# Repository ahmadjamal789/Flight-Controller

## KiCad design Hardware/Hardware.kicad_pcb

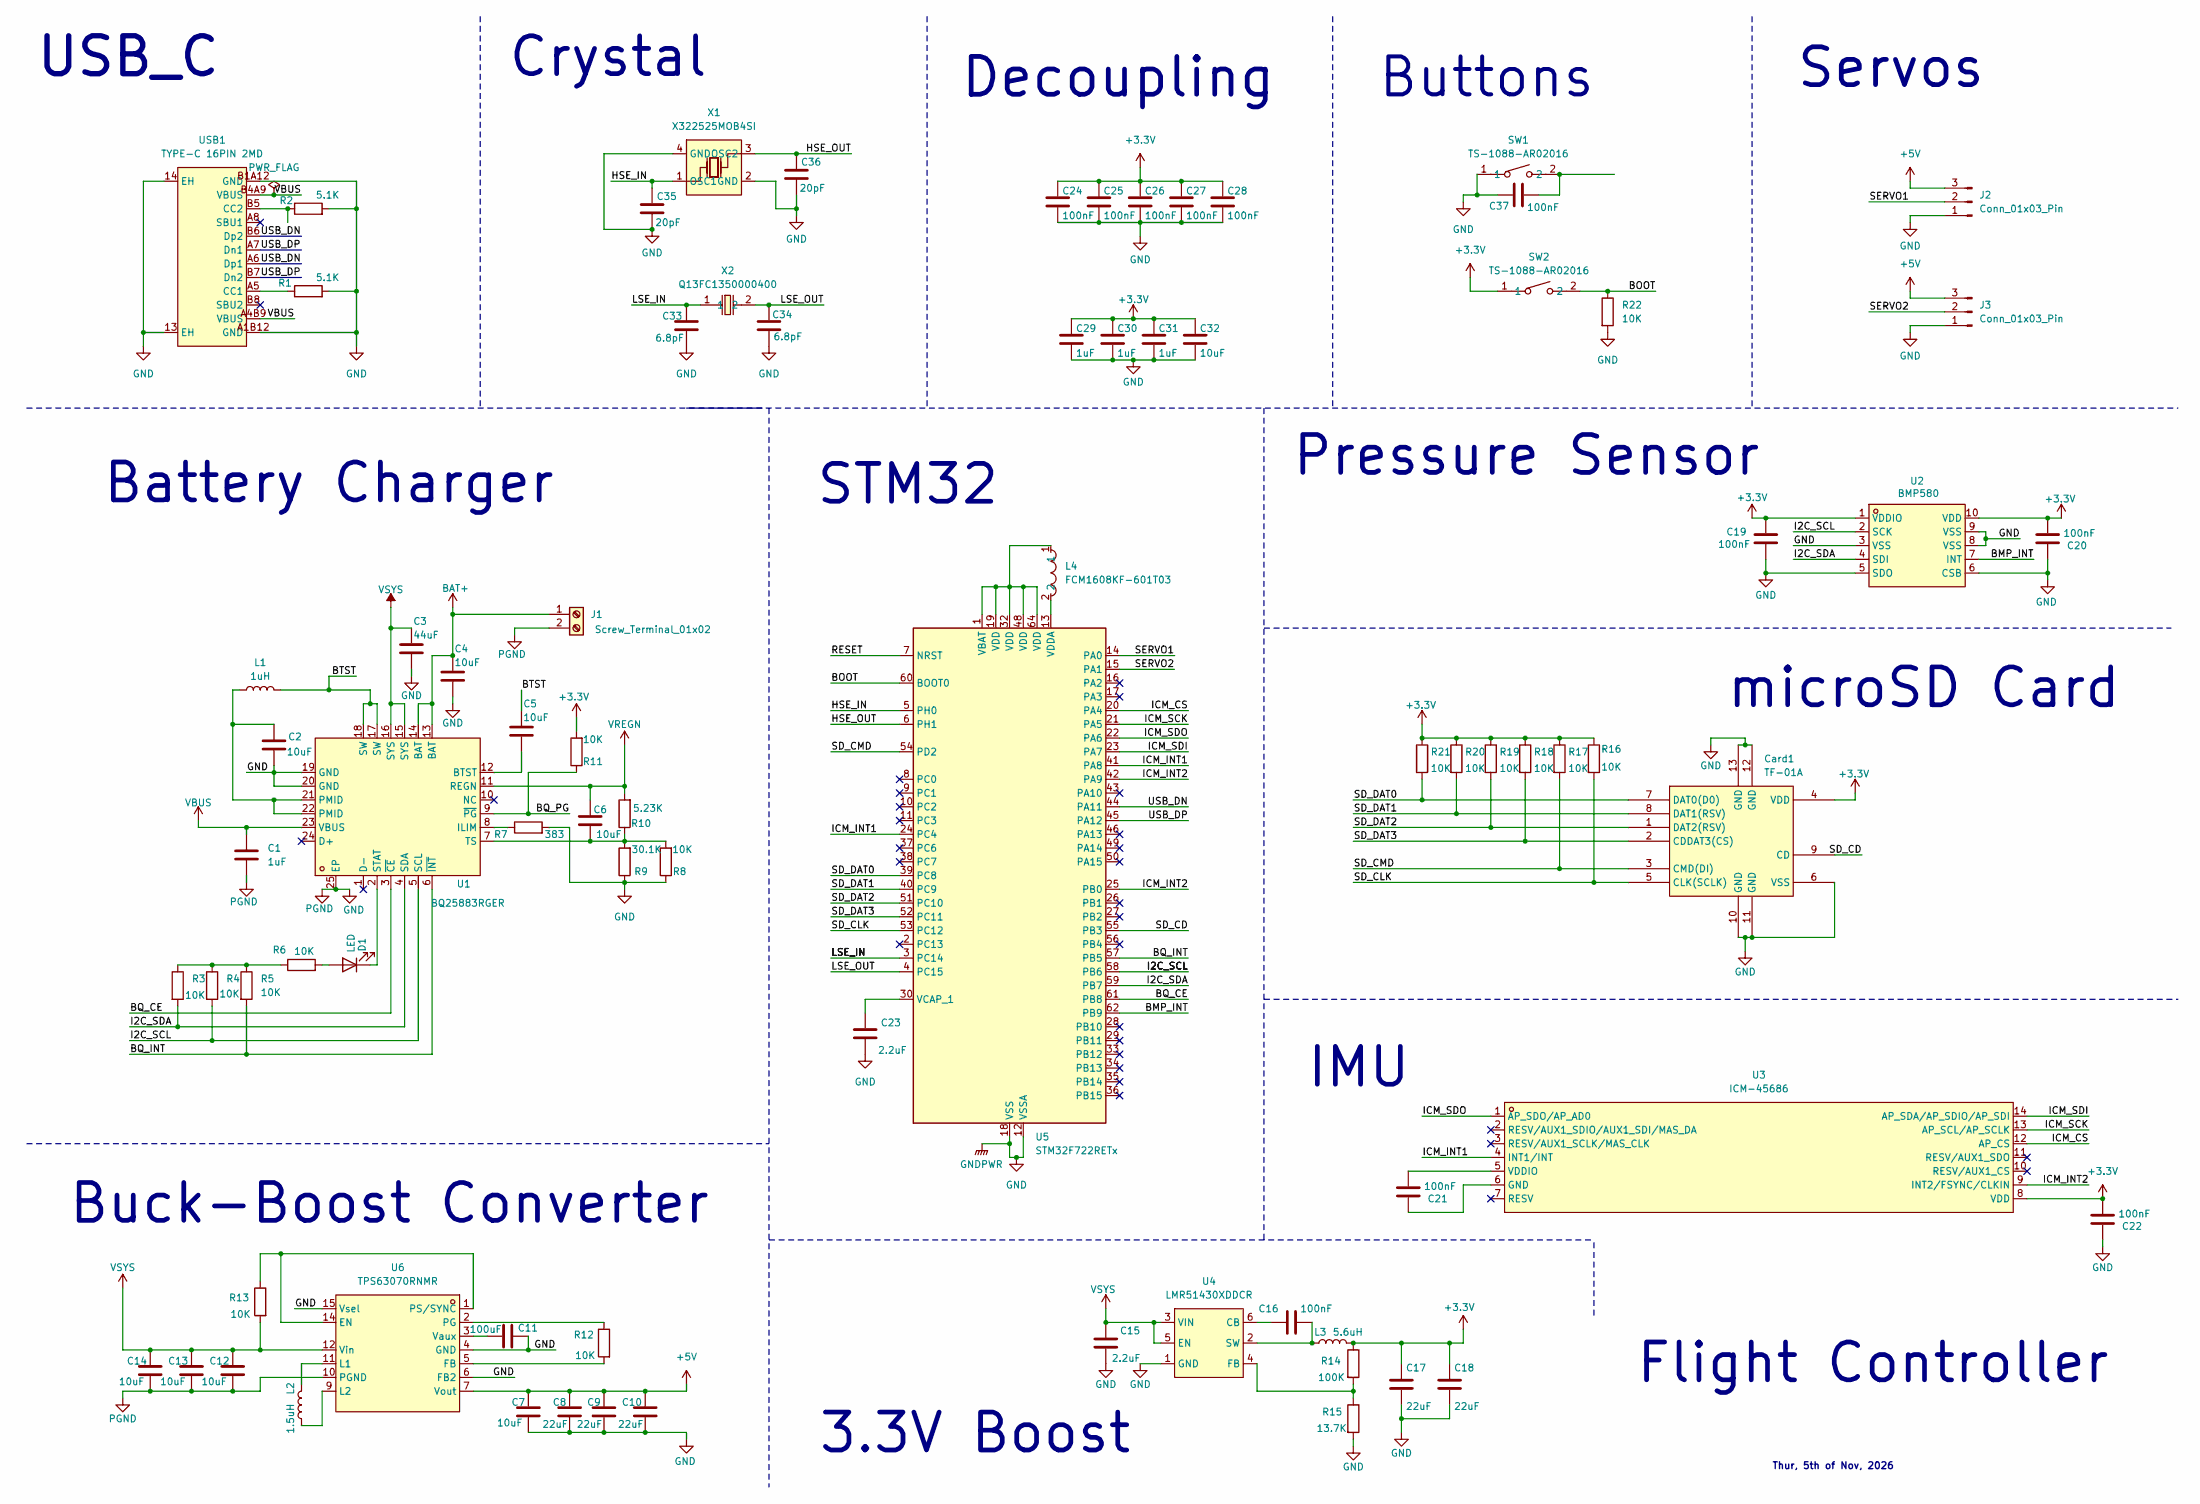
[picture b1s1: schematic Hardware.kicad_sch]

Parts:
C1, C29, C30: 1uF; C_0402_1005Metric
C2, C4, C5, C6, C7, C12, C13, C14, C32: 10uF; C_0805_2012Metric
C3: 44uF; C_0805_2012Metric
C8, C9, C10: 22uF; C_0805_2012Metric
C11: 100uF; C_01005_0402Metric
C15: 2.2uF; C_0201_0603Metric
C16, C19, C20, C21, C22, C24, C25, C26, C27, C28, C37: 100nF; C_0402_1005Metric
C17, C18: 22uF; C_0402_1005Metric
C23: 2.2uF; C_0402_1005Metric
C31: 1uF; C_0201_0603Metric
C33, C34: 6.8pF; C_0402_1005Metric
C35, C36: 20pF; C_0402_1005Metric
Card1: TF-01A; TF-SMD_TF-01A; MPN TF-01A; LCSC Part C91145
D1: LED; LED_0201_0603Metric
J1: Screw_Terminal_01x02; TerminalBlock_Xinya_XY308-2.54-2P_1x02_P2.54mm_Horizontal
J2, J3: Conn_01x03_Pin; PinHeader_1x03_P2.54mm_Vertical
L1: 1uH; L0603
L2: 1.5uH; L0603
L3: 5.6uH; L0603
L4: FCM1608KF-601T03; L0603; MPN FCM1608KF-601T03; LCSC Part C141723
R1, R2: 5.1K; R_0402_1005Metric
R3, R4, R5, R6, R8, R11, R12, R13, R16, R17, R18, R19, R20, R21, R22: 10K; R_0201_0603Metric
R7: 383; R_0201_0603Metric
R9: 30.1K; R_0402_1005Metric
R10: 5.23K; R_0201_0603Metric
R14: 100K; R_0402_1005Metric
R15: 13.7K; R_0201_0603Metric
SW1, SW2: TS-1088-AR02016; SW-SMD_L3.9-W3.0-P4.45; MPN TS-1088-AR02016; LCSC Part C720477
U1: BQ25883RGER; VFQFPN-24_L4.0-W4.0-P0.50-BL-EP2.8; MPN BQ25883RGER; LCSC Part C544362
U2: BMP580; LGA-10_L2.0-W2.0-P0.50-TL_BMP580; MPN BMP580; LCSC Part C22391138
U3: ICM-45686; LGA-14_L3.0-W2.5-P0.50-TL; MPN ICM-45686; LCSC Part C22459454
U4: LMR51430XDDCR; SOT-23-6_L2.9-W1.6-P0.95-LS2.8-BL; MPN LMR51430XDDCR; LCSC Part C5185863
U5: STM32F722RETx; LQFP-64_10x10mm_P0.5mm
U6: TPS63070RNMR; VQFN-15_L3.0-W2.5-P0.50-BL; MPN TPS63070RNMR; LCSC Part C109322
USB1: TYPE-C 16PIN 2MD; USB-C-SMD_TYPE-C-16PIN-2MD-073; MPN TYPE-C 16PIN 2MD(073); LCSC Part C2765186
X1: X322525MOB4SI; CRYSTAL-SMD_4P-L3.2-W2.5-BL; MPN X322525MOB4SI; LCSC Part C9006
X2: Q13FC1350000400; FC-135R_L3.2-W1.5; MPN Q13FC13500004; LCSC Part C32346

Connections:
+3.3V: C17.1, C18.1, C19.1, C20.2, C22.2, C24.1, C25.1, C26.1, C27.1, C28.1, C29.1, C30.1, C31.1, C32.1, Card1.4 (VDD), L3.2, R11.2, R14.1, R16.1, R17.1, R18.1, R19.1, R20.1, R21.1, SW2.1, U2.1 (VDDIO), U2.10 (VDD), U3.8 (VDD)
+5V: C7.1, C8.1, C9.1, C10.1, J2.3, J3.3, U6.7 (Vout)
/BMP_INT: U2.7 (INT), U5.62 (PB9)
/BOOT: R22.1, SW2.2, U5.60 (BOOT0)
/BQ_CE: U1.3 (~CE), U5.61 (PB8)
/BQ_INT: R5.2, U1.6 (~INT), U5.57 (PB5)
/BQ_PG: R11.1, U1.9 (~PG)
/BTST: C5.1, L1.2, U1.17 (SW), U1.18 (SW)
/HSE_IN: C35.1, U5.5 (PH0), X1.1 (OSC1)
/HSE_OUT: C36.1, U5.6 (PH1), X1.3 (OSC2)
/I2C_SCL: R4.2, U1.5 (SCL), U2.2 (SCK), U5.58 (PB6)
/I2C_SDA: R3.2, U1.4 (SDA), U2.4 (SDI), U5.59 (PB7)
/ICM_CS: U3.12 (AP_CS), U5.20 (PA4)
/ICM_INT1: U3.4 (INT1/INT), U5.24 (PC4), U5.41 (PA8)
/ICM_INT2: U3.9 (INT2/FSYNC/CLKIN), U5.25 (PB0), U5.42 (PA9)
/ICM_SCK: U3.13 (AP_SCL/AP_SCLK), U5.21 (PA5)
/ICM_SDI: U3.14 (AP_SDA/AP_SDIO/AP_SDI), U5.23 (PA7)
/ICM_SDO: U3.1 (AP_SDO/AP_AD0), U5.22 (PA6)
/LSE_IN: C33.1, U5.3 (PC14), X2.1
/LSE_OUT: C34.1, U5.4 (PC15), X2.2
/RESET: U5.7 (NRST)
/SD_CD: Card1.9 (CD), U5.55 (PB3)
/SD_CLK: Card1.5 (CLK(SCLK)), R16.2, U5.53 (PC12)
/SD_CMD: Card1.3 (CMD(DI)), R17.2, U5.54 (PD2)
/SD_DAT0: Card1.7 (DAT0(D0)), R21.2, U5.39 (PC8)
/SD_DAT1: Card1.8 (DAT1(RSV)), R20.2, U5.40 (PC9)
/SD_DAT2: Card1.1 (DAT2(RSV)), R19.2, U5.51 (PC10)
/SD_DAT3: Card1.2 (CDDAT3(CS)), R18.2, U5.52 (PC11)
/SERVO1: J2.2, U5.14 (PA0)
/SERVO2: J3.2, U5.15 (PA1)
/USB_DN: U5.44 (PA11), USB1.A6 (Dp1), USB1.B6 (Dp2)
/USB_DP: U5.45 (PA12), USB1.A7 (Dn1), USB1.B7 (Dn2)
BAT+: C4.1, J1.1, U1.13 (BAT), U1.14 (BAT)
GND: C1.2, C2.2, C3.2, C4.2, C7.2, C8.2, C9.2, C10.2, C11.1, C12.2, C13.2, C14.2, C15.2, C17.2, C18.2, C19.2, C20.1, C22.1, C23.2, C24.2, C25.2, C26.2, C27.2, C28.2, C29.2, C30.2, C31.2, C32.2, C33.2, C34.2, C35.2, C36.2, C37.1, Card1.6 (VSS), Card1.10 (GND), Card1.11 (GND), Card1.12 (GND), Card1.13 (GND), J1.2, J2.1, J3.1, R1.2, R2.2, R7.2, R8.1, R9.1, R15.2, R22.2, SW1.1, U1.19 (GND), U1.20 (GND), U1.25 (EP), U2.3 (VSS), U2.5 (SDO), U2.6 (CSB), U2.8 (VSS), U2.9 (VSS), U4.1 (GND), U5.12 (VSSA), U5.18 (VSS), U5.31 (VSS), U5.47 (VSS), U5.63 (VSS), U6.4 (GND), U6.6 (FB2), U6.10 (PGND), U6.15 (Vsel), USB1.13 (EH), USB1.14 (EH), USB1.A1B12 (GND), USB1.B1A12 (GND), X1.2 (GND), X1.4 (GND)
unnamed: C2.1, L1.1, U1.21 (PMID), U1.22 (PMID)
unnamed: C37.2, SW1.2
unnamed: D1.2 (A), R6.2
unnamed: D1.1 (K), U1.2 (STAT)
unnamed: R3.1, R4.1, R5.1, R6.1
unnamed: C5.2, U1.12 (BTST)
unnamed: R7.1, U1.8 (ILIM)
unnamed: C6.2, R8.2, R9.2, R10.1, U1.7 (TS)
unnamed: C21.1, U3.6 (GND)
unnamed: C21.2, U3.5 (VDDIO)
unnamed: C16.1, U4.6 (CB)
unnamed: R14.2, R15.1, U4.4 (FB)
unnamed: C16.2, L3.1, U4.2 (SW)
unnamed: L4.1, U5.1 (VBAT), U5.19 (VDD), U5.32 (VDD), U5.48 (VDD), U5.64 (VDD)
unnamed: C23.1, U5.30 (VCAP_1)
unnamed: L4.2, U5.13 (VDDA)
unnamed: R13.1, U6.1 (PS/SYNC), U6.14 (EN)
unnamed: R12.2, U6.5 (FB)
unnamed: L2.1, U6.11 (L1)
unnamed: L2.2, U6.9 (L2)
unnamed: R12.1, U6.2 (PG)
unnamed: C11.2, U6.3 (Vaux)
unnamed: R1.1, USB1.A5 (CC1)
unnamed: R2.1, USB1.B5 (CC2)
VBUS: C1.1, U1.23 (VBUS), USB1.A4B9 (VBUS), USB1.B4A9 (VBUS)
VREGN: C6.1, R10.2, U1.11 (REGN)
VSYS: C3.1, C12.1, C13.1, C14.1, C15.1, R13.2, U1.15 (SYS), U1.16 (SYS), U4.3 (VIN), U4.5 (EN), U6.12 (Vin)

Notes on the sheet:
Pressure Sensor
IMU
STM32
USB_C
Thur, 5th of Nov, 2026
Buck-Boost Converter
3.3V Boost
Buttons
Flight Controller
Crystal
Battery Charger
Servos
microSD Card
Decoupling

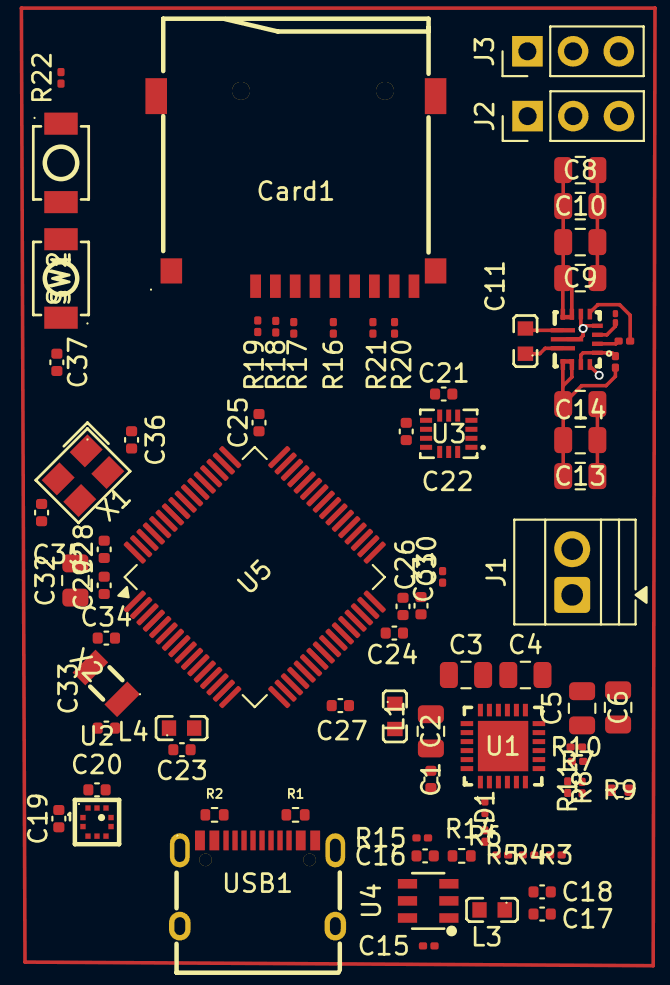
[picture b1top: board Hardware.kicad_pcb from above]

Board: 2 copper layers, 79 parts (0 on the bottom side), 60 nets.

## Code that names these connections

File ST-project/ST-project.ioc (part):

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Mcu.Name=STM32F722R(C-E)Tx
Mcu.Package=LQFP64
Mcu.UserName=STM32F722RETx
PA0-WKUP.Signal=S_TIM2_CH1_ETR
PA1.Signal=S_TIM2_CH2
PA11.Mode=Host_Only
PA11.Signal=USB_OTG_FS_DM
PA12.Mode=Host_Only
PA12.Signal=USB_OTG_FS_DP
PA4.Mode=NSS_Signal_Hard_Output
PA4.Signal=SPI1_NSS
PA5.Mode=Full_Duplex_Master
PA5.Signal=SPI1_SCK
PA6.Mode=Full_Duplex_Master
PA6.Signal=SPI1_MISO
PA7.Mode=Full_Duplex_Master
PA7.Signal=SPI1_MOSI
PB0.GPIOParameters=GPIO_Label
PB0.GPIO_Label=ICM_INT2
PB0.Signal=GPXTI0
PB3.GPIOParameters=GPIO_Label
PB3.GPIO_Label=SD_CD
PB3.Signal=GPIO_Input
PB5.GPIOParameters=GPIO_Label
PB5.GPIO_Label=BQ_INT
PB5.Signal=GPXTI5
PB6.Mode=I2C
PB6.Signal=I2C1_SCL
PB7.Mode=I2C
PB7.Signal=I2C1_SDA
PB8.GPIOParameters=GPIO_Label
PB8.GPIO_Label=BQ_CE
PB8.Signal=GPIO_Output
PB9.GPIOParameters=GPIO_Label
PB9.GPIO_Label=BMP_INT
PB9.Signal=GPXTI9
PC10.Mode=SD_4_bits_Wide_bus
PC10.Signal=SDMMC1_D2
PC11.Mode=SD_4_bits_Wide_bus
PC11.Signal=SDMMC1_D3
PC12.Mode=SD_4_bits_Wide_bus
PC12.Signal=SDMMC1_CK
PC14-OSC32_IN.Mode=LSE-External-Oscillator
PC14-OSC32_IN.Signal=RCC_OSC32_IN
PC15-OSC32_OUT.Mode=LSE-External-Oscillator
PC15-OSC32_OUT.Signal=RCC_OSC32_OUT
PC4.GPIOParameters=GPIO_Label
PC4.GPIO_Label=ICM_INT1
PC4.Signal=GPXTI4
PC8.Mode=SD_4_bits_Wide_bus
PC8.Signal=SDMMC1_D0
PC9.Mode=SD_4_bits_Wide_bus
PC9.Signal=SDMMC1_D1
PD2.Mode=SD_4_bits_Wide_bus
PD2.Signal=SDMMC1_CMD
PH0-OSC_IN.Mode=HSE-External-Oscillator
PH0-OSC_IN.Signal=RCC_OSC_IN
PH1-OSC_OUT.Mode=HSE-External-Oscillator
PH1-OSC_OUT.Signal=RCC_OSC_OUT
RCC.HSE_VALUE=25000000
board=custom
